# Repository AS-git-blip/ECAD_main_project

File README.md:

# ECAD_main_project
Пары по САПР электронных средств
Добавлена библитека компонетов для схемы системы оптического картирования 
Сделана схема системы для считывания сигналов оптической томографии
Создана печатная плата по схеме. Выполнена трассировка

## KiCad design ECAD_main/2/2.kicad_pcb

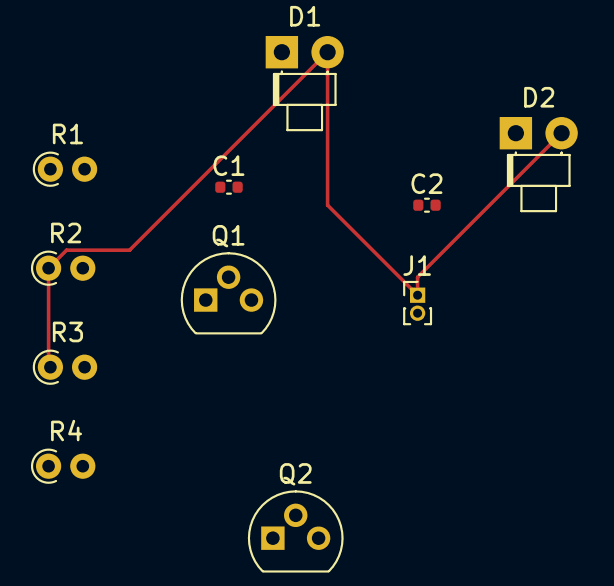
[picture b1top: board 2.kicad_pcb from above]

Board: 2 copper layers, 11 parts (0 on the bottom side), 7 nets.

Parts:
C1, C2: 10uF; C_0402_1005Metric
D1, D2: LED; LED_D1.8mm_W1.8mm_H2.4mm_Horizontal_O1.27mm_Z1.6mm
J1: Conn_01x02_Pin; PinHeader_1x02_P1.00mm_Vertical
Q1, Q2: КТ315Б; TO-92
R1, R4: 300; R_Axial_DIN0204_L3.6mm_D1.6mm_P1.90mm_Vertical
R2, R3: 27k; R_Axial_DIN0204_L3.6mm_D1.6mm_P1.90mm_Vertical

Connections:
+5V: D1.2 (A), D2.2 (A), J1.1, R2.1, R3.1
unnamed: C1.1, R1.2
unnamed: C1.2, R2.2
unnamed: C2.1, R4.2
unnamed: C2.2, R3.2
unnamed: D1.1 (K), R1.1
unnamed: D2.1 (K), R4.1

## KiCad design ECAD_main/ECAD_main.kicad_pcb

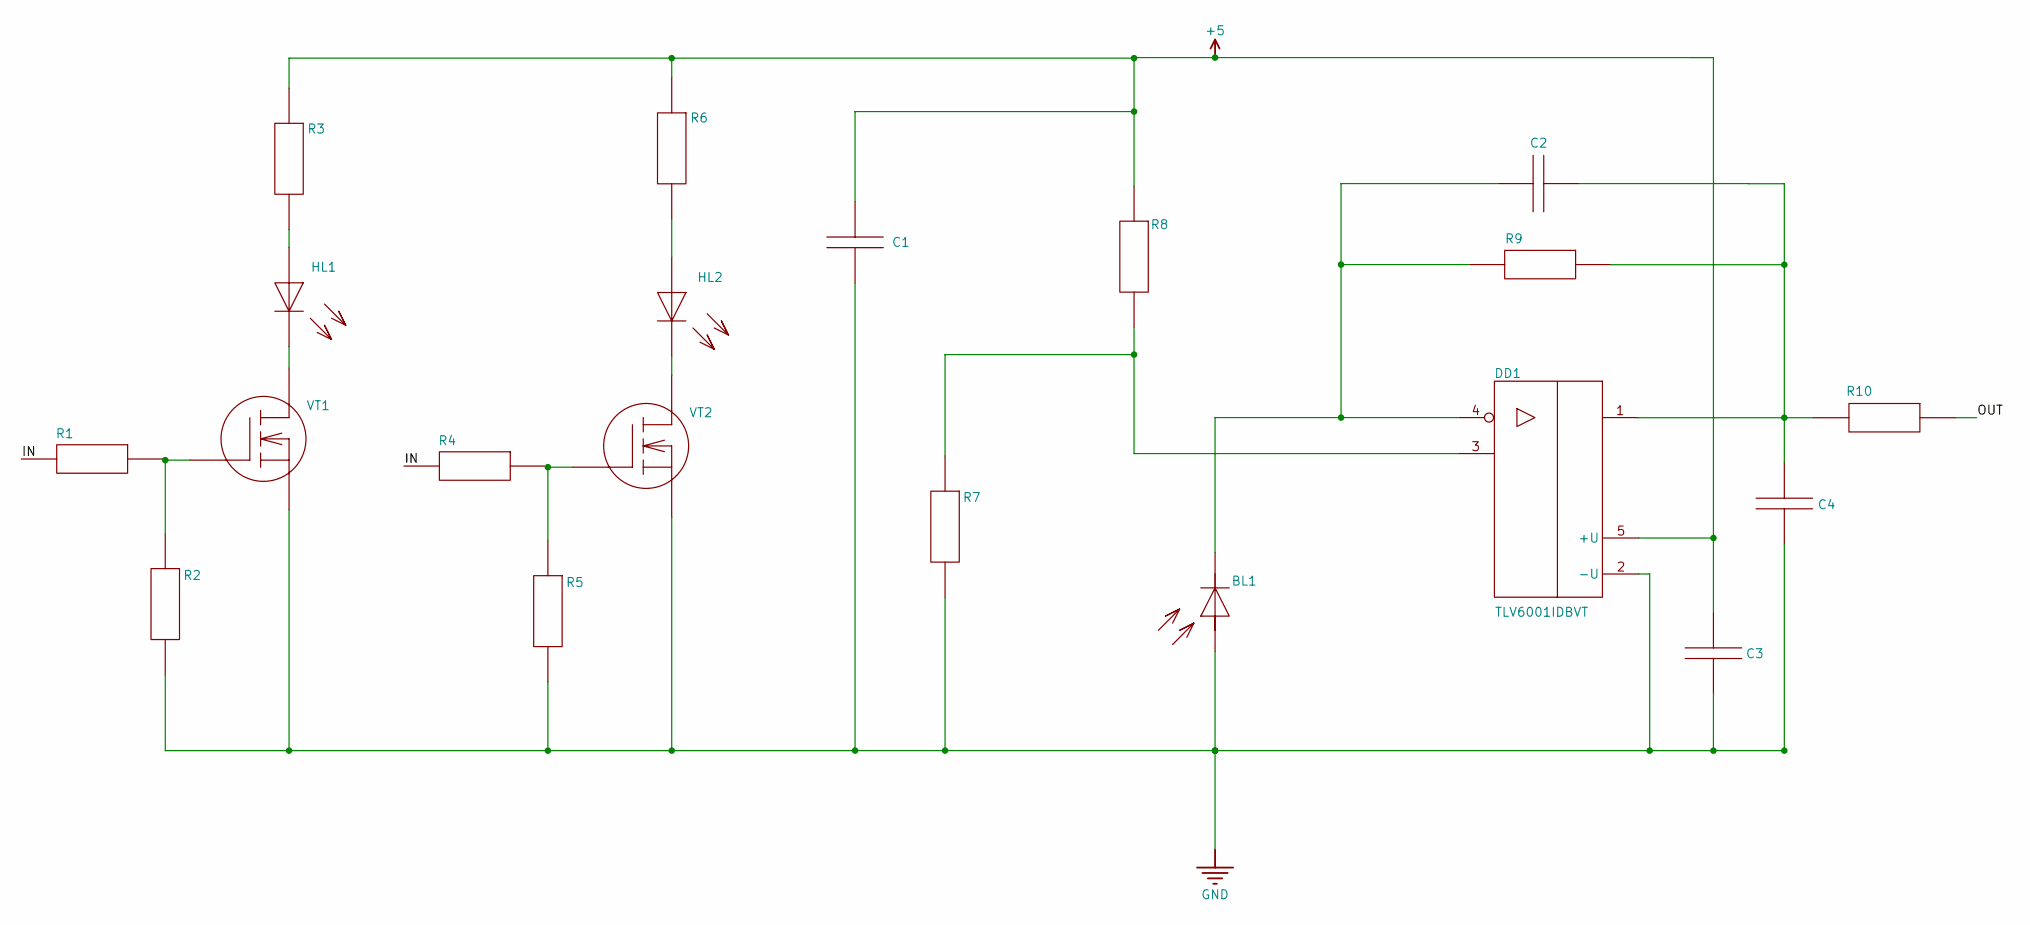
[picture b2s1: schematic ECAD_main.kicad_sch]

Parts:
BL1: Photodiode; BPW34
C1, C2, C3, C4: Capacitor; C1206
DD1: TLV6001IDBVT; TLV6001
HL1, HL2: LED; VSMY2850RG
R1, R2, R3, R4, R5, R6, R7, R8, R9, R10: Resistor; R0603
VT1, VT2: IRLML6244TRPBF; IRLML

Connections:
+5: C1.2, C3.2, DD1.5 (+U), R3.2, R6.1, R8.2
GND: BL1.1, C1.1, C3.1, C4.1, DD1.2 (-U), R2.1, R5.1, R7.1, VT1.2 (S), VT2.2 (S)
IN: R1.1, R4.1
unnamed: BL1.2, C2.2, DD1.4, R9.2
unnamed: C2.1, C4.2, DD1.1, R9.1, R10.2
unnamed: DD1.3, R7.2, R8.1
unnamed: HL1.1, R3.1
unnamed: HL2.1, R6.2
unnamed: HL1.2, VT1.3 (D)
unnamed: R1.2, R2.2, VT1.1 (G)
unnamed: HL2.2, VT2.3 (D)
unnamed: R4.2, R5.2, VT2.1 (G)
OUT: R10.1

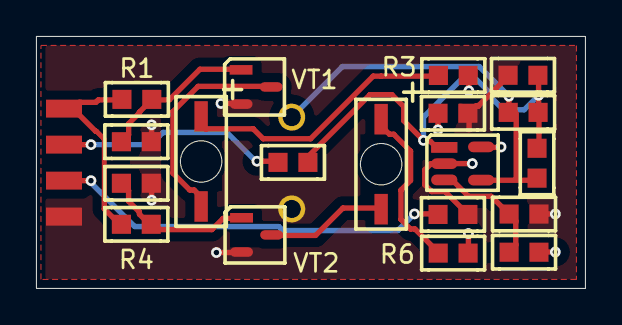
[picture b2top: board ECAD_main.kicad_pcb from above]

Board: 2 copper layers, 30.5 x 14.0 mm, 20 parts (1 on the bottom side), 12 nets.

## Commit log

2025-09-14 Added libraries submodule
2025-09-14 Создали проект, добавили библиотеки
2025-10-31 Добавлена схема, сделана трассировка платы
2025-10-31 Добавлена схема, сделана трассировка
2025-10-31 Удалены лишние компоненты
2025-10-31 Удалены лишние компоненты 2
2025-10-31 Добавлен файл .bat для автоматизации генерации файлов gerber
2025-10-31 Добавлен и изменен файл .bat для автоматизации генерации файлов gerber
